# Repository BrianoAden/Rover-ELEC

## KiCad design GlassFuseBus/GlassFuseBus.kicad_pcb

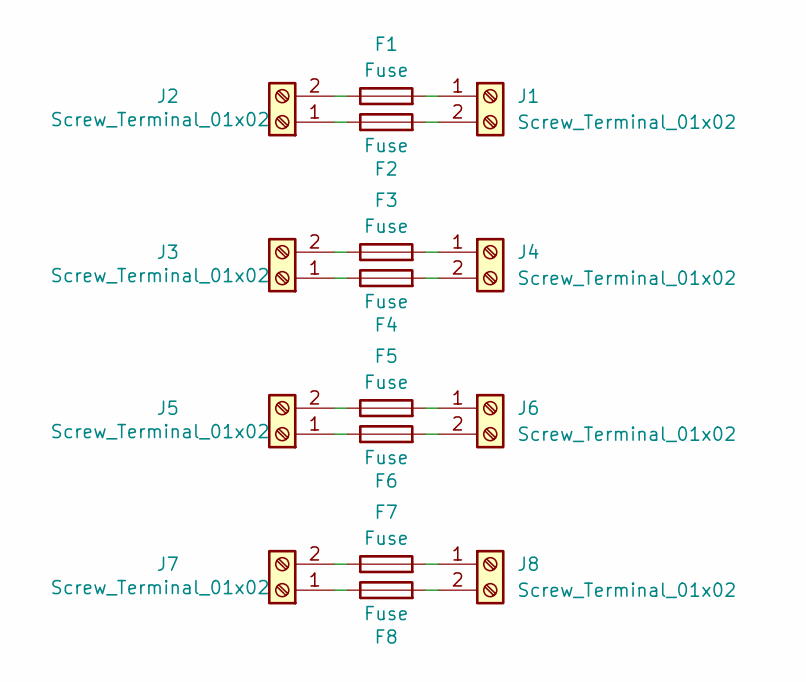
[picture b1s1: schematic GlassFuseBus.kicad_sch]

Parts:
F1, F2, F3, F4, F5, F6, F7, F8: Fuse; BLX-A 5x20 Fuse
J1, J2, J3, J4, J5, J6, J7, J8: Screw_Terminal_01x02; Altech_AK100_1x02_P5.00mm

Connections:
unnamed: F1.2, J1.1
unnamed: F2.2, J1.2
unnamed: F2.1, J2.1
unnamed: F1.1, J2.2
unnamed: F4.1, J3.1
unnamed: F3.1, J3.2
unnamed: F3.2, J4.1
unnamed: F4.2, J4.2
unnamed: F6.1, J5.1
unnamed: F5.1, J5.2
unnamed: F5.2, J6.1
unnamed: F6.2, J6.2
unnamed: F8.1, J7.1
unnamed: F7.1, J7.2
unnamed: F7.2, J8.1
unnamed: F8.2, J8.2

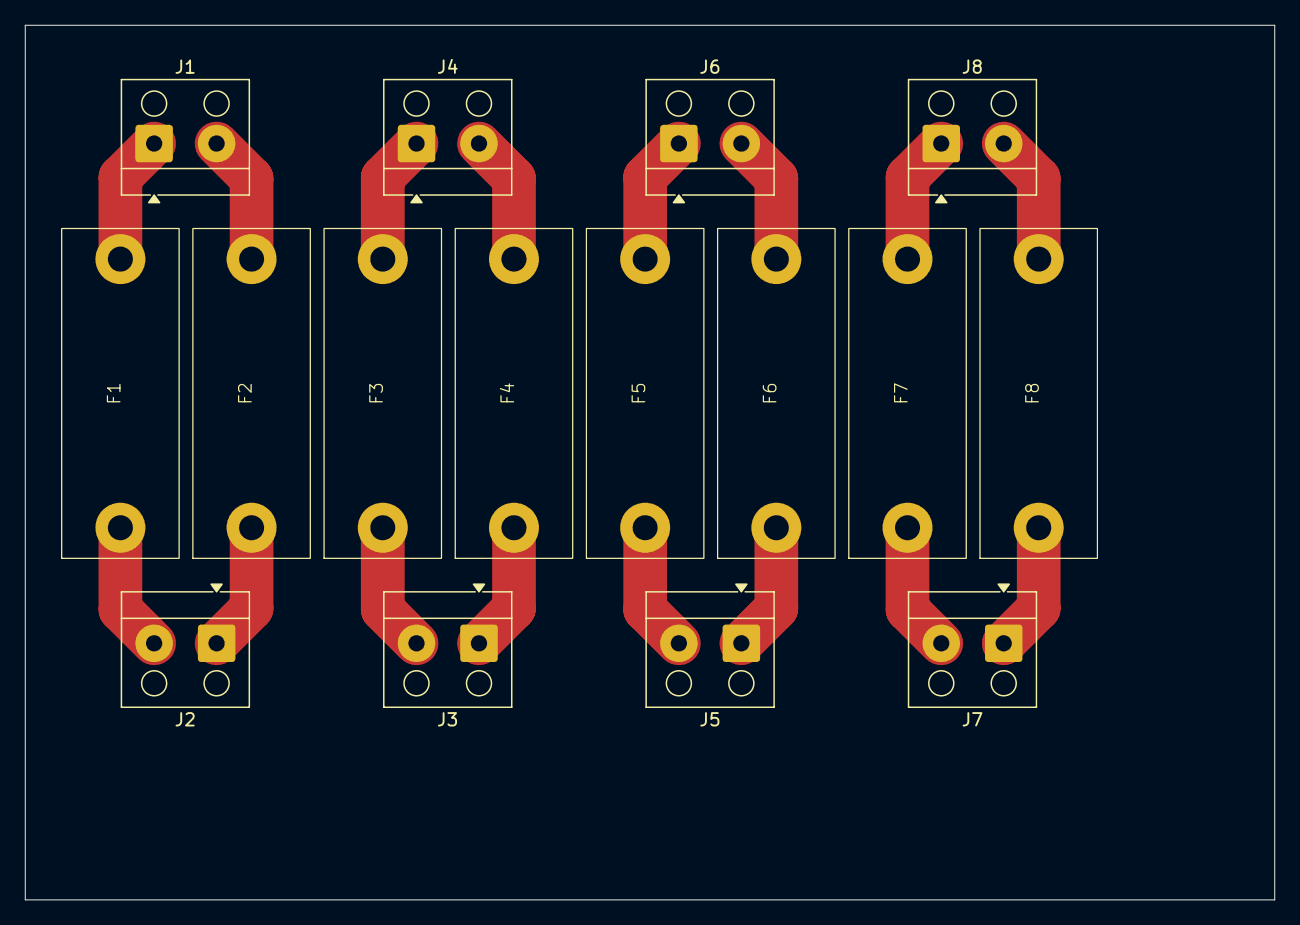
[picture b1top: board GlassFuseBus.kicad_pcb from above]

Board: 2 copper layers, 100.0 x 70.0 mm, 16 parts (0 on the bottom side), 16 nets.

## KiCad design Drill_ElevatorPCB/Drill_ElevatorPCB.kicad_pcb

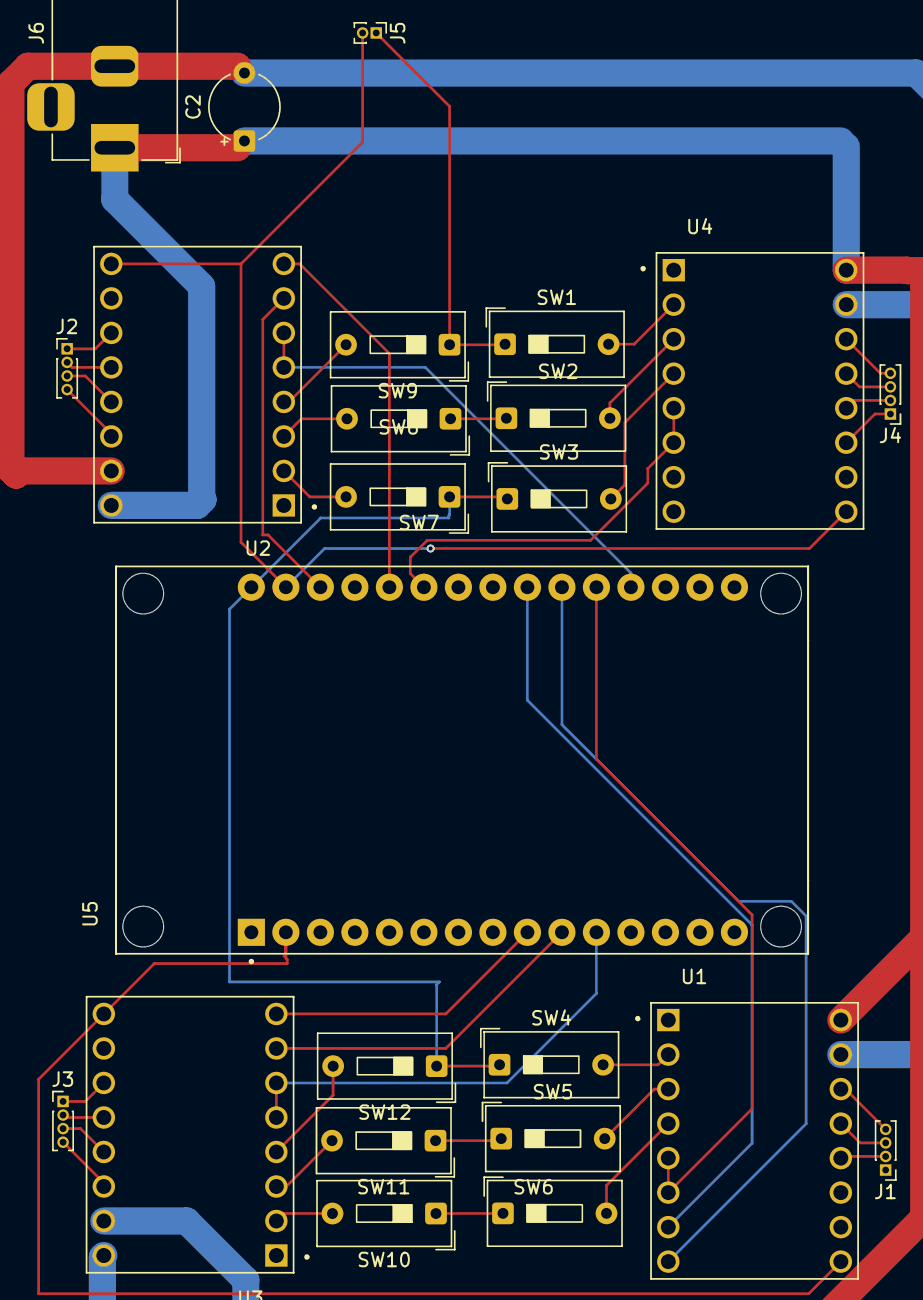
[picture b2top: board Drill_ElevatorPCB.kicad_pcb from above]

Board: 2 copper layers, 24 parts (0 on the bottom side), 44 nets.

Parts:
C2: C_Polarized; CP_Radial_Tantal_D5.0mm_P5.00mm
J1, J2, J3, J4: Conn_01x04_Socket; PinHeader_1x04_P1.00mm_Vertical
J5: Conn_01x02_Socket; PinHeader_1x02_P1.00mm_Vertical
J6: Barrel_Jack; BarrelJack_Horizontal
SW1, SW2, SW3, SW4, SW5, SW6, SW7, SW8, SW9, SW10, SW11, SW12: SW_DIP_x01; SW_DIP_SPSTx01_Slide_9.78x4.72mm_W7.62mm_P2.54mm
U1, U2, U3, U4: DRV8825_STEPPER_MOTOR_DRIVER_CARRIER; IC_DRV8825_STEPPER_MOTOR_DRIVER_CARRIER
U5: ESP32-DEVKIT-V1; MODULE_ESP32_DEVKIT_V1

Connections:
+3.3V: J5.1, SW1.1, SW2.1, SW3.1, SW4.1, SW5.1, SW6.1, SW7.1, SW8.1, SW9.1, SW10.1, SW11.1, SW12.1, U5.30 (VIN)
+12V: C2.1, J6.1, U1.16 (VMOT), U2.16 (VMOT), U3.16 (VMOT), U4.16 (VMOT)
GND: J5.2, U1.9 (GND), U2.9 (GND), U3.9 (GND), U4.9 (GND), U5.2 (GND), U5.29 (GND)
GND2: C2.2, J6.2, U1.15 (GND_MOT), U2.15 (GND_MOT), U3.15 (GND_MOT), U4.15 (GND_MOT)
unnamed: J1.1, U1.11 (A2)
unnamed: J1.2, U1.12 (A1)
unnamed: J1.3, U1.13 (B1)
unnamed: J1.4, U1.14 (B2)
unnamed: J2.1, U2.11 (A2)
unnamed: J2.2, U2.12 (A1)
unnamed: J2.3, U2.13 (B1)
unnamed: J2.4, U2.14 (B2)
unnamed: J3.1, U3.11 (A2)
unnamed: J3.2, U3.12 (A1)
unnamed: J3.3, U3.13 (B1)
unnamed: J3.4, U3.14 (B2)
unnamed: J4.1, U4.11 (A2)
unnamed: J4.2, U4.12 (A1)
unnamed: J4.3, U4.13 (B1)
unnamed: J4.4, U4.14 (B2)
unnamed: SW4.2, U1.2 (M0)
unnamed: SW5.2, U1.3 (M1)
unnamed: SW6.2, U1.4 (M2)
unnamed: SW7.2, U2.2 (M0)
unnamed: SW8.2, U2.3 (M1)
unnamed: SW9.2, U2.4 (M2)
unnamed: SW10.2, U3.2 (M0)
unnamed: SW11.2, U3.3 (M1)
unnamed: SW12.2, U3.4 (M2)
unnamed: SW1.2, U4.2 (M0)
unnamed: SW2.2, U4.3 (M1)
unnamed: SW3.2, U4.4 (M2)
SLP/RST 1: U1.5 (~RST), U1.6 (~SLP), U5.20 (D35)
SLP/RST 2: U2.5 (~RST), U2.6 (~SLP), U5.19 (D34)
SLP/RST 3: U3.5 (~RST), U3.6 (~SLP), U5.11 (D21)
SLP/RST 4: U4.5 (~RST), U4.6 (~SLP), U5.25 (D27)
dir_1: U1.8 (DIR), U5.21 (D32)
dir_2: U2.8 (DIR), U5.26 (D14)
dir_3: U3.8 (DIR), U5.9 (D18)
dir_4: U4.8 (DIR), U5.24 (D26)
step_1: U1.7 (STEP), U5.22 (D33)
step_2: U2.7 (STEP), U5.28 (D13)
step_3: U3.7 (STEP), U5.10 (D19)
step_4: U4.7 (STEP), U5.23 (D25)

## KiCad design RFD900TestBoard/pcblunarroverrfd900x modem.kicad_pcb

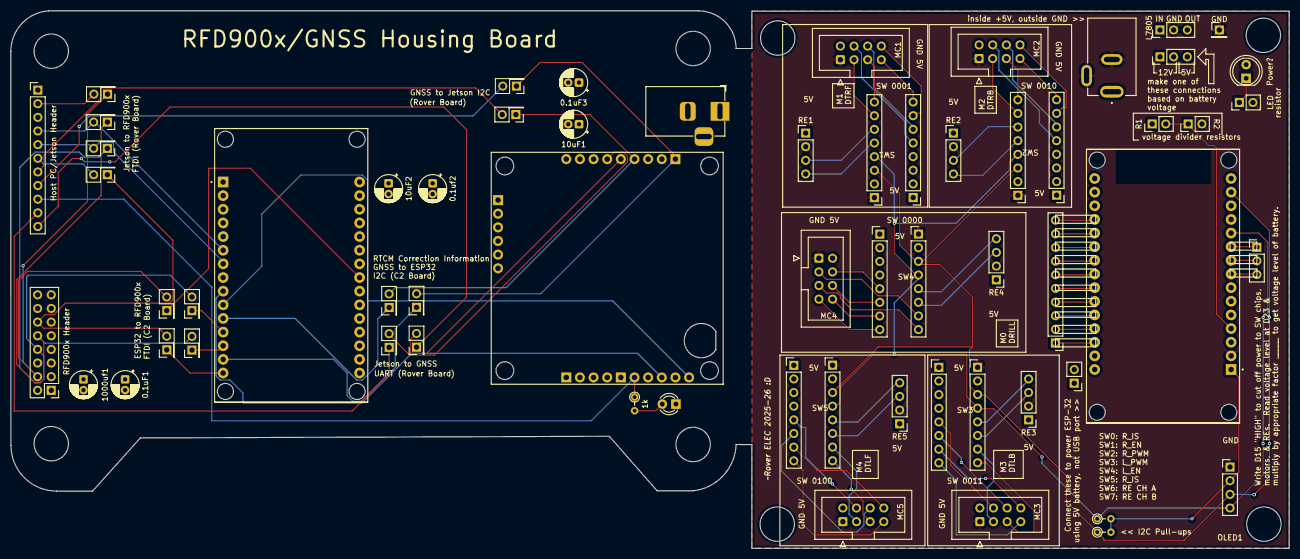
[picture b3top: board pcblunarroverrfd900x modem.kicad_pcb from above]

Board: 4 copper layers, 238.0 x 100.1 mm, 57 parts (0 on the bottom side), 88 nets.

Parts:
0.1uF1, 0.1uF3, 0.1uf2, 10uF1, 10uF2, 1000uf1: C_Polarized_US; CP_Radial_D5.0mm_P2.00mm
1k: 1k; R_Axial_DIN0204_L3.6mm_D1.6mm_P2.54mm_Vertical
D1: LED; LED_D5.0mm
D1#2: LED; LED_D3.0mm
J1: DC-005-5A-2.0; XKB_DC-005-5A-2.0
J1#2: Barrel_Jack_Switch; BarrelJack_Horizontal
J2: Conn_01x01_Pin; PinHeader_1x01_P2.54mm_Vertical
J2#2: Conn_02x08_Counter_Clockwise; PinHeader_2x08_P2.54mm_Vertical
J3, J4#2, J5#2, J6#2, J7, J8, J9, J10, J11, J12, J13, J14, J16, J17: Conn_02x01; PinHeader_2x01_P2.54mm_Vertical
J4: Conn_01x10_Socket; PinHeader_1x10_P2.54mm_Vertical
J5: Conn_01x03_Socket; PinHeader_1x03_P2.54mm_Vertical
J6: Conn_01x02_Socket; PinHeader_1x02_P2.54mm_Vertical
J7#2: Conn_01x03_Pin; PinHeader_1x03_P2.54mm_Vertical
J18: Conn_01x11; PinHeader_1x11_P2.54mm_Vertical
MC1, MC2, MC3, MC4, MC5: Conn_02x04_Counter_Clockwise; 16_pin_custom_wraparound_connector
OLED1: Conn_01x04; PinHeader_1x04_P2.54mm_Vertical
R1, R2: R_Small_US; R_Axial_DIN0204_L3.6mm_D1.6mm_P2.54mm_Vertical
R3, R4, R5: R_Small_US; PinHeader_1x02_P2.54mm_Vertical
RE1, RE2, RE3, RE4, RE5: Conn_01x04; PinHeader_1x04_P2.54mm_Vertical
SW1, SW2, SW3, SW4, SW5: MAX11617; sw_pcb0029
U1, U1#2: ESP32-DEVKIT-V1; MODULE_ESP32_DEVKIT_V1
U2: GPS-15136; MODULE_GPS-15136
U3: L7805; PinHeader_1x03_P2.54mm_Vertical

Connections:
3.3V: OLED1.2, R1.2, R2.2, U1#2.1 (3V3)
5V: D1.2 (A), J6.1, J7#2.3, MC1.8, MC2.8, MC3.8, MC4.8, MC5.8, RE1.1, RE2.1, RE3.1, RE4.1, RE5.1, SW1.15 (GND), SW2.15 (GND), SW3.15 (GND), SW4.15 (GND), SW5.15 (GND), U3.3 (OUT)
+5V: 0.1uF1.1, 0.1uF3.1, 0.1uf2.1, 10uF1.1, 10uF2.1, 1000uf1.1, J1#2.1, J2#2.3, U1.30 (VIN), U2.J7_8 (5V_J7)
CTS-esp: J3.1, U1.23 (D25)
CTS-jet: J10.2, J18.2
ESP32Feeder: J6.2, U1#2.30 (VIN)
GND: 0.1uF1.2, 0.1uF3.2, 0.1uf2.2, 10uF1.2, 10uF2.2, 1000uf1.2, D1#2.1 (K), J1.2, J1.3, J1#2.2, J2.1, J2#2.2, J18.1, MC1.1, MC2.1, MC3.1, MC4.1, MC5.1, OLED1.1, R3.2, R5.2, RE1.2, RE2.2, RE3.2, RE4.2, RE5.2, SW1.16 (Vdd), SW2.16 (Vdd), SW3.16 (Vdd), SW4.16 (Vdd), SW5.16 (Vdd), U1.2 (GND), U1.29 (GND), U1#2.2 (GND), U2.J1_6 (GND_J1), U2.J7_9 (GND_J7), U3.2 (GND)
INT: U1.10 (D19), U2.J6_6 (INT)
unnamed: 1k.2, D1#2.2 (A)
unnamed: D1.1 (K), R5.1
unnamed: J2#2.8, J4#2.2, J8.1
unnamed: J2#2.10, J5#2.2, J9.1
unnamed: J2#2.12, J6#2.2, J7.1
unnamed: J4.1, U1#2.28 (D13)
unnamed: J4.2, U1#2.27 (D12)
unnamed: J4.3, U1#2.26 (D14)
unnamed: J4.4, U1#2.25 (D27)
unnamed: J4.5, U1#2.24 (D26)
unnamed: J4.6, U1#2.23 (D25)
unnamed: J4.7, U1#2.22 (D33)
unnamed: J4.8, U1#2.21 (D32)
unnamed: J4.9, U1#2.20 (D35)
unnamed: J4.10, U1#2.19 (D34)
unnamed: J5.1, U1#2.10 (D19)
unnamed: J5.2, U1#2.9 (D18)
unnamed: J5.3, U1#2.8 (D5)
unnamed: J7#2.1, U3.1 (IN)
unnamed: J2#2.4, J3.2, J10.1
unnamed: J11.1, J14.2, U2.J7_4 (SDA/~CS_J7)
unnamed: J12.1, J13.2, U2.J7_1 (SCL/SCK_J7)
unnamed: J16.2, U2.J7_6 (TX2_J7)
unnamed: J17.2, U2.J7_5 (RX2_J7)
unnamed: MC1.2, SW1.10 (AIN5)
unnamed: MC1.3, SW1.9 (AIN4)
unnamed: MC1.4, SW1.8 (AIN3)
unnamed: MC1.5, SW1.7 (AIN2)
unnamed: MC1.6, SW1.6 (AIN1)
unnamed: MC1.7, SW1.5 (AIN0)
unnamed: MC2.2, SW2.10 (AIN5)
unnamed: MC2.3, SW2.9 (AIN4)
unnamed: MC2.4, SW2.8 (AIN3)
unnamed: MC2.5, SW2.7 (AIN2)
unnamed: MC2.6, SW2.6 (AIN1)
unnamed: MC2.7, SW2.5 (AIN0)
unnamed: MC3.2, SW3.10 (AIN5)
unnamed: MC3.3, SW3.9 (AIN4)
unnamed: MC3.4, SW3.8 (AIN3)
unnamed: MC3.5, SW3.7 (AIN2)
unnamed: MC3.6, SW3.6 (AIN1)
unnamed: MC3.7, SW3.5 (AIN0)
unnamed: MC4.2, SW4.10 (AIN5)
unnamed: MC4.3, SW4.9 (AIN4)
unnamed: MC4.4, SW4.8 (AIN3)
unnamed: MC4.5, SW4.7 (AIN2)
unnamed: MC4.6, SW4.6 (AIN1)
unnamed: MC4.7, SW4.5 (AIN0)
unnamed: MC5.2, SW5.10 (AIN5)
unnamed: MC5.3, SW5.9 (AIN4)
unnamed: MC5.4, SW5.8 (AIN3)
unnamed: MC5.5, SW5.7 (AIN2)
unnamed: MC5.6, SW5.6 (AIN1)
unnamed: MC5.7, SW5.5 (AIN0)
unnamed: RE1.3, SW1.11 (AIN6)
unnamed: RE1.4, SW1.12 (AIN7)
unnamed: RE2.3, SW2.11 (AIN6)
unnamed: RE2.4, SW2.12 (AIN7)
unnamed: RE3.3, SW3.11 (AIN6)
unnamed: RE3.4, SW3.12 (AIN7)
unnamed: RE4.3, SW4.11 (AIN6)
unnamed: RE4.4, SW4.12 (AIN7)
unnamed: RE5.3, SW5.11 (AIN6)
unnamed: RE5.4, SW5.12 (AIN7)
unnamed: R3.1, R4.2, U1#2.4 (D2)
RST: U1.9 (D18), U2.J6_4 (~RESET)
RTK-jet: 1k.1, J18.9, U2.J6_2 (RTK_STAT)
RTS-esp: J6#2.1, U1.15 (D23)
RTS-jet: J7.2, J18.6
RX2-jet: J16.1, J18.10
RX-esp: J4#2.1, U1.12 (RX0)
RX-jet: J8.2, J18.5, U1.7 (TX2)
SCL: J13.1, OLED1.3, R1.1, SW1.14 (SDA), SW2.14 (SDA), SW3.14 (SDA), SW4.14 (SDA), SW5.14 (SDA), U1.14 (D22), U1#2.14 (D22)
SCL-jet: J12.2, J18.8
SDA: J14.1, OLED1.4, R2.1, SW1.13 (SCL), SW2.13 (SCL), SW3.13 (SCL), SW4.13 (SCL), SW5.13 (SCL), U1.11 (D21), U1#2.11 (D21)
SDA-jet: J11.2, J18.7
TX2-jet: J17.1, J18.11
TX-esp: J5#2.1, U1.13 (TX0)
TX-jet: J9.2, J18.4, U1.6 (RX2)
Vin: J1.1, J7#2.2, R4.1

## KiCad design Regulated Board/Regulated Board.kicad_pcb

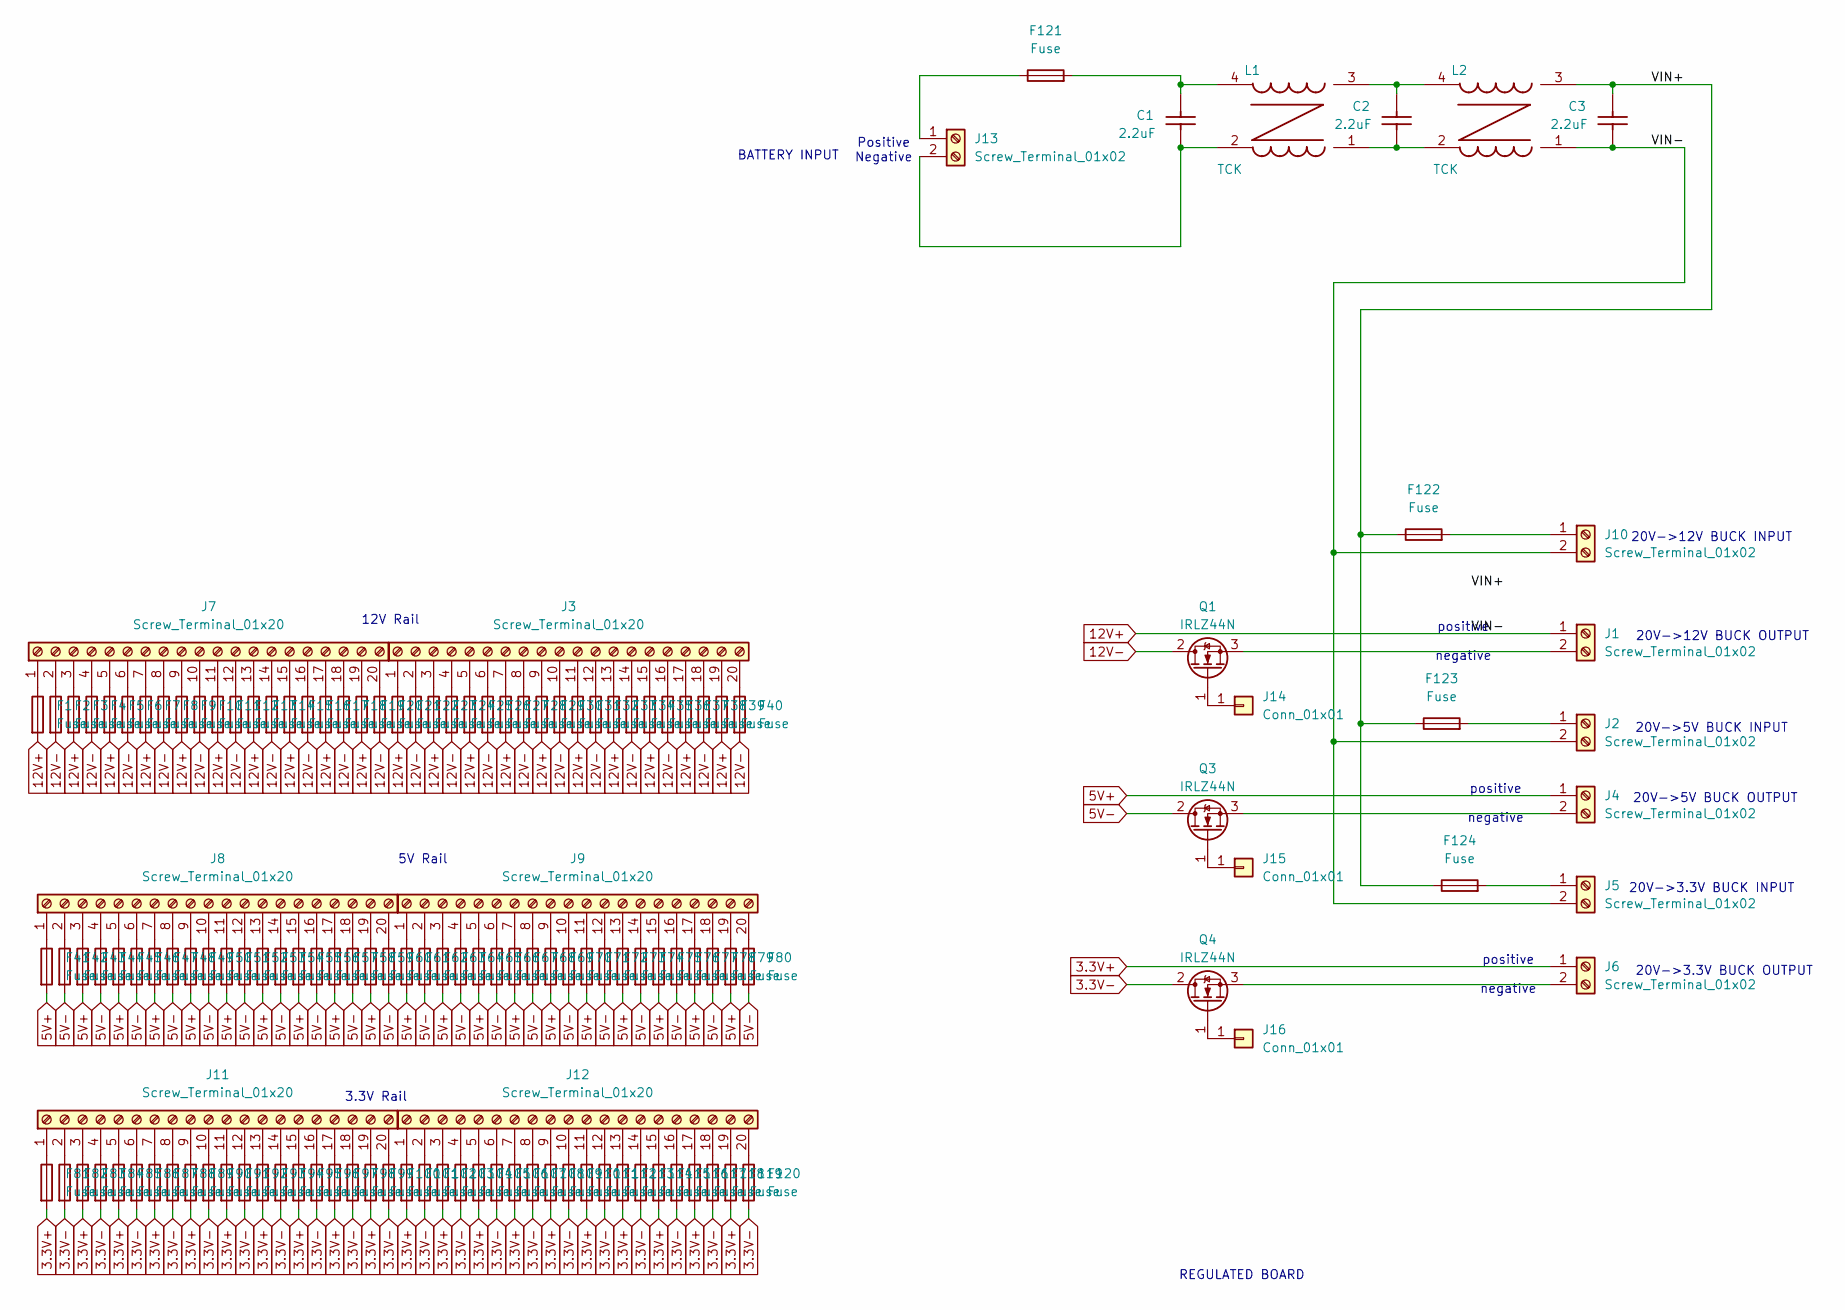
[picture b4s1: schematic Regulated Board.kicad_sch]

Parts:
C1, C2, C3: 2.2uF; CP_Radial_D5.0mm_P2.00mm
F1, F2, F3, F4, F5, F6, F7, F8, F9, F10, F11, F12, F13, F14, F15, F16, F17, F18, F19, F20, F21, F22, F23, F24, F25, F26, F27, F28, F29, F30, F31, F32, F33, F34, F35, F36, F37, F38, F39, F40, F41, F42, F43, F44, F45, F46, F47, F48, F49, F50, F51, F52, F53, F54, F55, F56, F57, F58, F59, F60, F61, F62, F63, F64, F65, F66, F67, F68, F69, F70, F71, F72, F73, F74, F75, F76, F77, F78, F79, F80, F81, F82, F83, F84, F85, F86, F87, F88, F89, F90, F91, F92, F93, F94, F95, F96, F97, F98, F99, F100, F101, F102, F103, F104, F105, F106, F107, F108, F109, F110, F111, F112, F113, F114, F115, F116, F117, F118, F119, F120, F121, F122, F123, F124: Fuse; FUSE_3544-2
J1, J2, J4, J5, J6, J10, J13: Screw_Terminal_01x02; PinHeader_1x02_P2.54mm_Vertical
J3, J7, J8, J9, J11, J12: Screw_Terminal_01x20
J14, J15, J16: Conn_01x01; PinHeader_1x01_P2.54mm_Vertical
L1: TCK; TCK-076; Part Number TCK-053
L2: TCK; TCK-076; Part Number TCK-076
Q1, Q3, Q4: IRLZ44N; TO-220-3_Vertical

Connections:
3.3V+: F81.2, F83.2, F85.2, F87.2, F89.2, F91.2, F93.2, F95.2, F97.2, F99.2, F101.2, F103.2, F105.2, F107.2, F109.2, F111.2, F113.2, F115.2, F117.2, F119.2, J6.1
3.3V-: F82.2, F84.2, F86.2, F88.2, F90.2, F92.2, F94.2, F96.2, F98.2, F100.2, F102.2, F104.2, F106.2, F108.2, F110.2, F112.2, F114.2, F116.2, F118.2, F120.2, Q4.2 (D)
5V+: F41.2, F43.2, F45.2, F47.2, F49.2, F51.2, F53.2, F55.2, F57.2, F59.2, F61.2, F63.2, F65.2, F67.2, F69.2, F71.2, F73.2, F75.2, F77.2, F79.2, J4.1
5V-: F42.2, F44.2, F46.2, F48.2, F50.2, F52.2, F54.2, F56.2, F58.2, F60.2, F62.2, F64.2, F66.2, F68.2, F70.2, F72.2, F74.2, F76.2, F78.2, F80.2, Q3.2 (D)
12V+: C3.2, F1.2, F3.2, F5.2, F7.2, F9.2, F11.2, F13.2, F15.2, F17.2, F19.2, F21.2, F23.2, F25.2, F27.2, F29.2, F31.2, F33.2, F35.2, F37.2, F39.2, J1.1, J2.2, J5.2, J10.2, L2.1
12V-: F2.2, F4.2, F6.2, F8.2, F10.2, F12.2, F14.2, F16.2, F18.2, F20.2, F22.2, F24.2, F26.2, F28.2, F30.2, F32.2, F34.2, F36.2, F38.2, F40.2, Q1.2 (D)
/VIN+: C3.1, F122.1, F123.1, F124.1, L2.3 (1)
unnamed: C1.1, F121.2, L1.4 (2)
unnamed: C2.1, L1.3 (1), L2.4 (2)
unnamed: C2.2, L1.1, L2.2
unnamed: J1.2, Q1.3 (S)
unnamed: F123.2, J2.1
unnamed: F21.1, J3.1
unnamed: F22.1, J3.2
unnamed: F23.1, J3.3
unnamed: F24.1, J3.4
unnamed: F25.1, J3.5
unnamed: F26.1, J3.6
unnamed: F27.1, J3.7
unnamed: F28.1, J3.8
unnamed: F29.1, J3.9
unnamed: F30.1, J3.10
unnamed: F31.1, J3.11
unnamed: F32.1, J3.12
unnamed: F33.1, J3.13
unnamed: F34.1, J3.14
unnamed: F35.1, J3.15
unnamed: F36.1, J3.16
unnamed: F37.1, J3.17
unnamed: F38.1, J3.18
unnamed: F39.1, J3.19
unnamed: F40.1, J3.20
unnamed: J4.2, Q3.3 (S)
unnamed: F124.2, J5.1
unnamed: J6.2, Q4.3 (S)
unnamed: F1.1, J7.1
unnamed: F2.1, J7.2
unnamed: F3.1, J7.3
unnamed: F4.1, J7.4
unnamed: F5.1, J7.5
unnamed: F6.1, J7.6
unnamed: F7.1, J7.7
unnamed: F8.1, J7.8
unnamed: F9.1, J7.9
unnamed: F10.1, J7.10
unnamed: F11.1, J7.11
unnamed: F12.1, J7.12
unnamed: F13.1, J7.13
unnamed: F14.1, J7.14
unnamed: F15.1, J7.15
unnamed: F16.1, J7.16
unnamed: F17.1, J7.17
unnamed: F18.1, J7.18
unnamed: F19.1, J7.19
unnamed: F20.1, J7.20
unnamed: F41.1, J8.1
unnamed: F42.1, J8.2
unnamed: F43.1, J8.3
unnamed: F44.1, J8.4
unnamed: F45.1, J8.5
unnamed: F46.1, J8.6
unnamed: F47.1, J8.7
unnamed: F48.1, J8.8
unnamed: F49.1, J8.9
unnamed: F50.1, J8.10
unnamed: F51.1, J8.11
unnamed: F52.1, J8.12
unnamed: F53.1, J8.13
unnamed: F54.1, J8.14
unnamed: F55.1, J8.15
unnamed: F56.1, J8.16
unnamed: F57.1, J8.17
unnamed: F58.1, J8.18
unnamed: F59.1, J8.19
unnamed: F60.1, J8.20
unnamed: F61.1, J9.1
unnamed: F62.1, J9.2
unnamed: F63.1, J9.3
unnamed: F64.1, J9.4
unnamed: F65.1, J9.5
unnamed: F66.1, J9.6
unnamed: F67.1, J9.7
unnamed: F68.1, J9.8
unnamed: F69.1, J9.9
unnamed: F70.1, J9.10
unnamed: F71.1, J9.11
unnamed: F72.1, J9.12
unnamed: F73.1, J9.13
unnamed: F74.1, J9.14
unnamed: F75.1, J9.15
unnamed: F76.1, J9.16
unnamed: F77.1, J9.17
unnamed: F78.1, J9.18
unnamed: F79.1, J9.19
unnamed: F80.1, J9.20
unnamed: F122.2, J10.1
unnamed: F81.1, J11.1
unnamed: F82.1, J11.2
unnamed: F83.1, J11.3
unnamed: F84.1, J11.4
unnamed: F85.1, J11.5
unnamed: F86.1, J11.6
unnamed: F87.1, J11.7
unnamed: F88.1, J11.8
unnamed: F89.1, J11.9
unnamed: F90.1, J11.10
unnamed: F91.1, J11.11
unnamed: F92.1, J11.12
unnamed: F93.1, J11.13
unnamed: F94.1, J11.14
unnamed: F95.1, J11.15
unnamed: F96.1, J11.16
unnamed: F97.1, J11.17
unnamed: F98.1, J11.18
unnamed: F99.1, J11.19
unnamed: F100.1, J11.20
unnamed: F101.1, J12.1
unnamed: F102.1, J12.2
unnamed: F103.1, J12.3
unnamed: F104.1, J12.4
unnamed: F105.1, J12.5
unnamed: F106.1, J12.6
unnamed: F107.1, J12.7
unnamed: F108.1, J12.8
unnamed: F109.1, J12.9
unnamed: F110.1, J12.10
unnamed: F111.1, J12.11
unnamed: F112.1, J12.12
unnamed: F113.1, J12.13
unnamed: F114.1, J12.14
unnamed: F115.1, J12.15
unnamed: F116.1, J12.16
unnamed: F117.1, J12.17
unnamed: F118.1, J12.18
unnamed: F119.1, J12.19
unnamed: F120.1, J12.20
unnamed: F121.1, J13.1
unnamed: C1.2, J13.2, L1.2
unnamed: J14.1, Q1.1 (G)
unnamed: J15.1, Q3.1 (G)
unnamed: J16.1, Q4.1 (G)

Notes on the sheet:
12V Rail
20V->12V BUCK OUTPUT
positive negative
Positive Negative
REGULATED BOARD
20V->5V BUCK OUTPUT
20V->5V BUCK INPUT
3.3V Rail
20V->3.3V BUCK OUTPUT
5V Rail
20V->12V BUCK INPUT
20V->3.3V BUCK INPUT
BATTERY INPUT

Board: 2 copper layers, 142 parts (0 on the bottom side), 21 nets, no tracks yet.

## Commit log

2025-02-04 fixed branches
2025-02-11 fixed branches AGAIN
2025-02-20 fixed branches...
2025-02-20 The serial_commands library should work
2025-02-20 Version of arm motor driver that compiles
2025-02-22 Arm Motor Driver works
2025-02-23 Motor Driver now writes to a screen
2025-03-02 Velocity Mode updated to ino
2025-03-03 added move_forward command
2025-03-03 stuff
2025-03-03 New Wheel Driver
2025-03-03 Attempt to fix code for testing
2025-03-04 hw-039 code added
2025-03-04 Updated arm driver with acceleration (temp)
2025-03-05 Lots of work converting the motor driver to a better version. (Still does not work)
2025-03-06 Added Library for BTS7960 Motor Controller
2025-03-06 Circuit Diagram Finished
2025-03-08 Working acceleration for the arm motor driver
2025-03-09 Arm Driver Button works
2025-03-22 Lots of stuff moved to unused and a lot of commands added to the wheel driver
2025-03-24 Updates to the wheel driver
2025-03-25 Drill Driver
2025-03-25 Changed command id of drill speed command
2025-04-08 Serial Test Success
2025-04-09 Versbose Wheel Driver
2025-04-17 Bodge with serial passthrough
2025-08-01 Best working version
2025-08-28 Added tests for rover movement and showcase
2025-09-19 Started work on shift register library
2025-09-22 Added code for Small Baby rover
2025-09-26 made edits to motor controller code
2025-09-29 Fixed shift register test
2025-10-24 Added code in setup to test motors
2025-10-24 Added code to test motor
2025-12-03 Update Rover_DrivetrainHallEffectRotaryEncoderTest.ino
    Added RPM
2025-12-03 Created Power_PCBs
2025-12-04 Added more fuses
2025-12-04 Updated PDF
2025-12-05 Assigned footprints to all components
2025-12-05 Added a lot of footprints and did some PCB layout
    Need to find footprints and appropriate screw terminals. Will route.
2025-12-21 Some Tests
2026-01-02 Motor Control PCB for Drivetrain & Drill Motors
2026-01-03 Added copper paths to PCB
2026-01-03 Modified pcb text
2026-01-03 made screw holes less likely to break
2026-01-03 Filled ground on all layers
2026-01-03 Corrected devkit footprint
2026-01-03 Skeleton of final motor control code for drivetrain and drill. Very far from finished
2026-01-04 made esp32 power from battery optional
2026-01-06 Added linear regulator
2026-01-06 fixed a few labels
2026-01-14 Added motor control
2026-01-14 Final
2026-01-14 idk it told me to commit
2026-01-15 misc
2026-01-16 Added GND pin, connected REs to SW
2026-01-16 movement library in progress
2026-01-18 Fixed stuff
2026-01-20 New motor test
2026-01-21 Turns RS02
2026-01-21 Misc RS02 stuff
2026-01-23 Made3motorsSpin
2026-01-23 started RFD900x Test Board PCB
2026-01-23 edits
2026-01-25 made changes to RFD900x test board
2026-01-26 some changes to RFD900x Housing
2026-01-28 final pushes
2026-01-28 added jumpers to RFD900x Housing Board
2026-01-28 almost done with RFD900x Test Board
2026-01-28 made final touches to schematic
2026-01-30 Misc motor control pcb stuff
2026-02-01 made some changes to the layout of the RFD900x housing board
2026-02-03 made final changes to RFD900x Housing Board
2026-02-04 Big big sigmaballs
    Balls
2026-02-04 hello!!!!!!!!
2026-02-04 generated gbr and drill files for manufacturing
2026-02-05 panelized rfd and motor controller pcb for ordering
2026-02-07 added JLCPCB design rules
2026-02-13 added test code for movement motors
2026-02-18 Start
2026-02-21 schematicDone
2026-02-22 made changes to SW Test, drivetrain control code, and added I2C Scanner
2026-02-22 Finalized schematic
2026-02-22 foot prints assigend
2026-02-23 added code for Jetson to command drivetrain through ESP32
2026-02-23 hello
2026-02-23 Glass Fuce Bus PCB Done
2026-02-24 Organized the REPO
2026-02-24 made code for controller encoding
2026-02-24 Added script to control Robstride Actuators over CAN with Jetson
2026-02-27 consolidated arm + drivetrain control
2026-02-27 adjusted receiver code
2026-02-27 made changes to sender code
2026-02-28 added stepper functionality for arm
2026-02-28 added stepper receive functionality
2026-02-28 reorganized
2026-02-28 added Servo controller code
2026-02-28 add servo
2026-02-28 added ESP32 code
2026-02-28 integrated stepper control code
2026-02-28 rearranging
2026-02-28 integrated majority of control into one script
2026-03-06 added code to send the camera with nanostationm2s
2026-03-06 dhthtd
2026-04-01 nothing significant
2026-04-08 unzipped pcb file
2026-04-14 I2C to control drivetrain and drill motors via esp32 from jetson
